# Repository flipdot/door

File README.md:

# door

Door control system for the flipdot hackspace. It runs on a Raspberry Pi at the
door together with a custom PCB in Raspberry Pi HAT form factor
(`pihat_door`).

The current door control system is
**[flipdot/flipdoor](https://code.flipdot.org/flipdot/flipdoor)**, a Rust
project with web and SSH interfaces that serves
[door.flipdot.space](https://door.flipdot.space). The Python implementation in
this repository is legacy and no longer maintained. The sections below
document that implementation and the hardware, which remain useful for
reference.

The system:

- continuously reads the door state (open/closed) from a switch on the door
- unlocks/locks the door on request
  - from a [web frontend](https://door.flipdot.space) (flipdot LDAP login,
    opening is restricted to flipdot members)
  - via RFID: members scan their card with a USB RFID reader
  - via MQTT close commands
- publishes the door state to `api.flipdot.org`, where it is displayed on the
  flipdot.org status page

## Repository layout

| Path | Description |
| --- | --- |
| `hardware/` | KiCad project for the `pihat_door` PCB |
| `door_firmware.X/` | Firmware for the PIC microcontroller on the HAT (MPLAB X project, XC8, PIC16LF1719) |
| `door_lib.py` | Shared Python library: serial access, door state, open/close, API update |
| `web.py` | Flask web frontend (login via LDAP, door state, open/close) |
| `mqtt2door.py` | MQTT bridge + RFID reader daemon |
| `door.py` | Small script that reads the door state and logs it to syslog |
| `door_state.sh` | Shell helper that reads the door state from the serial port |
| `acme.py`, `acme.sh/` | (legacy) TLS via Let's Encrypt/acme.sh; TLS is now handled by nginx |
| `door-master.nginx.conf` | Example nginx configuration (TLS, reverse proxy) |
| `web.service`, `mqtt2door.service` | systemd units |
| `sync.sh` | Syncs `authorized_keys` for the `opendoor` user from LDAP |
| `sync_rfid_tags.sh` | Regenerates `rfid_tags.json` (employee numbers) from LDAP |
| `config.example.py` | Configuration template (copy to `config.py`, see below) |

The `ldap_user/` and `acme.sh/` submodules provide LDAP authentication and
certificate handling respectively.

## Hardware and serial protocol

The HAT carries a PIC16LF1719 that is wired to the Raspberry Pi GPIO header.
It talks over a UART at 9600 baud 8N1 (`config.SERIAL`, default
`/dev/ttyAMA0`).

The PIC continuously samples the door switch (ADC, averaged over 30 samples)
and prints one line per batch:

```
<adc> - <ra0>\r\n
```

- `<adc>`: 10-bit average of the door switch reading; values `> 500` mean the
  door is **open**
- `<ra0>`: digital input on pin RA0

Commands (single character, no newline required):

- `1` – pulse the door open (~200 ms)
- `0` – pulse the door closed (~200 ms)
- anything else – echoed back

The PIC sends `b` at startup and `r` (followed by a UART re-init) when it hits
a UART over-error. `door_lib.get_state()` skips lines that do not start with a
number, so these are handled transparently.

## Web frontend

`web.py` is a small Flask app:

- login with flipdot LDAP credentials (`ldap_user` submodule)
- shows the current door state (10 s cache, or fake data when
  `config.fake_door` is set)
- "open door" button – only usable by flipdot members
  (`is_member` LDAP attribute)
- "close door" button

```sh
pip install -r requirements.txt
cp config.example.py config.py  # adjust DOMAIN, EMAIL, SERIAL, ...
./web.py
```

For production it runs under systemd (`web.service`) behind nginx
(`door-master.nginx.conf`), which terminates TLS.

Set `fake_door = True` in `config.py` to run the app without the hardware.

## MQTT and RFID

`mqtt2door.py` (run under systemd as `mqtt2door.service`) does three things:

1. Connects to the MQTT broker at `power.flipdot.space:1883` and closes the
   door on the `actor/door/close` topic (plus a raw ESP sensor topic).
2. Polls the USB RFID reader on `/dev/ttyUSB0`. If the scanned tag is in
   `rfid_tags.json`, the door is opened, otherwise the event is only logged.
   `sync_rfid_tags.sh` regenerates `rfid_tags.json` from the `employeeNumber`
   attributes of all LDAP members, so member cards work automatically.
3. Publishes the door state to
   `https://api.flipdot.org/sensors/door/locked/<0|1>` every 60 seconds.

## Firmware

`door_firmware.X/` is an MPLAB X project for the PIC16LF1719 on the HAT
(build with the XC8 compiler, e.g. via MPLAB X IDE). See
`hardware/pihat_door.pro` for the board design.

## Configuration

Copy `config.example.py` to `config.py` (git-ignored) and adjust:

| Key | Meaning |
| --- | --- |
| `PORT`, `HTTPS_PORT` | Ports for the Flask app |
| `SERIAL` | Serial device of the HAT, e.g. `/dev/ttyAMA0` |
| `DOMAIN`, `EMAIL` | Domain and contact for certificate issuance |
| `DEBUG` | Verbose logging |
| `STAGING` | Use the Let's Encrypt staging server |
| `fake_door` | Simulate the door state (for development) |

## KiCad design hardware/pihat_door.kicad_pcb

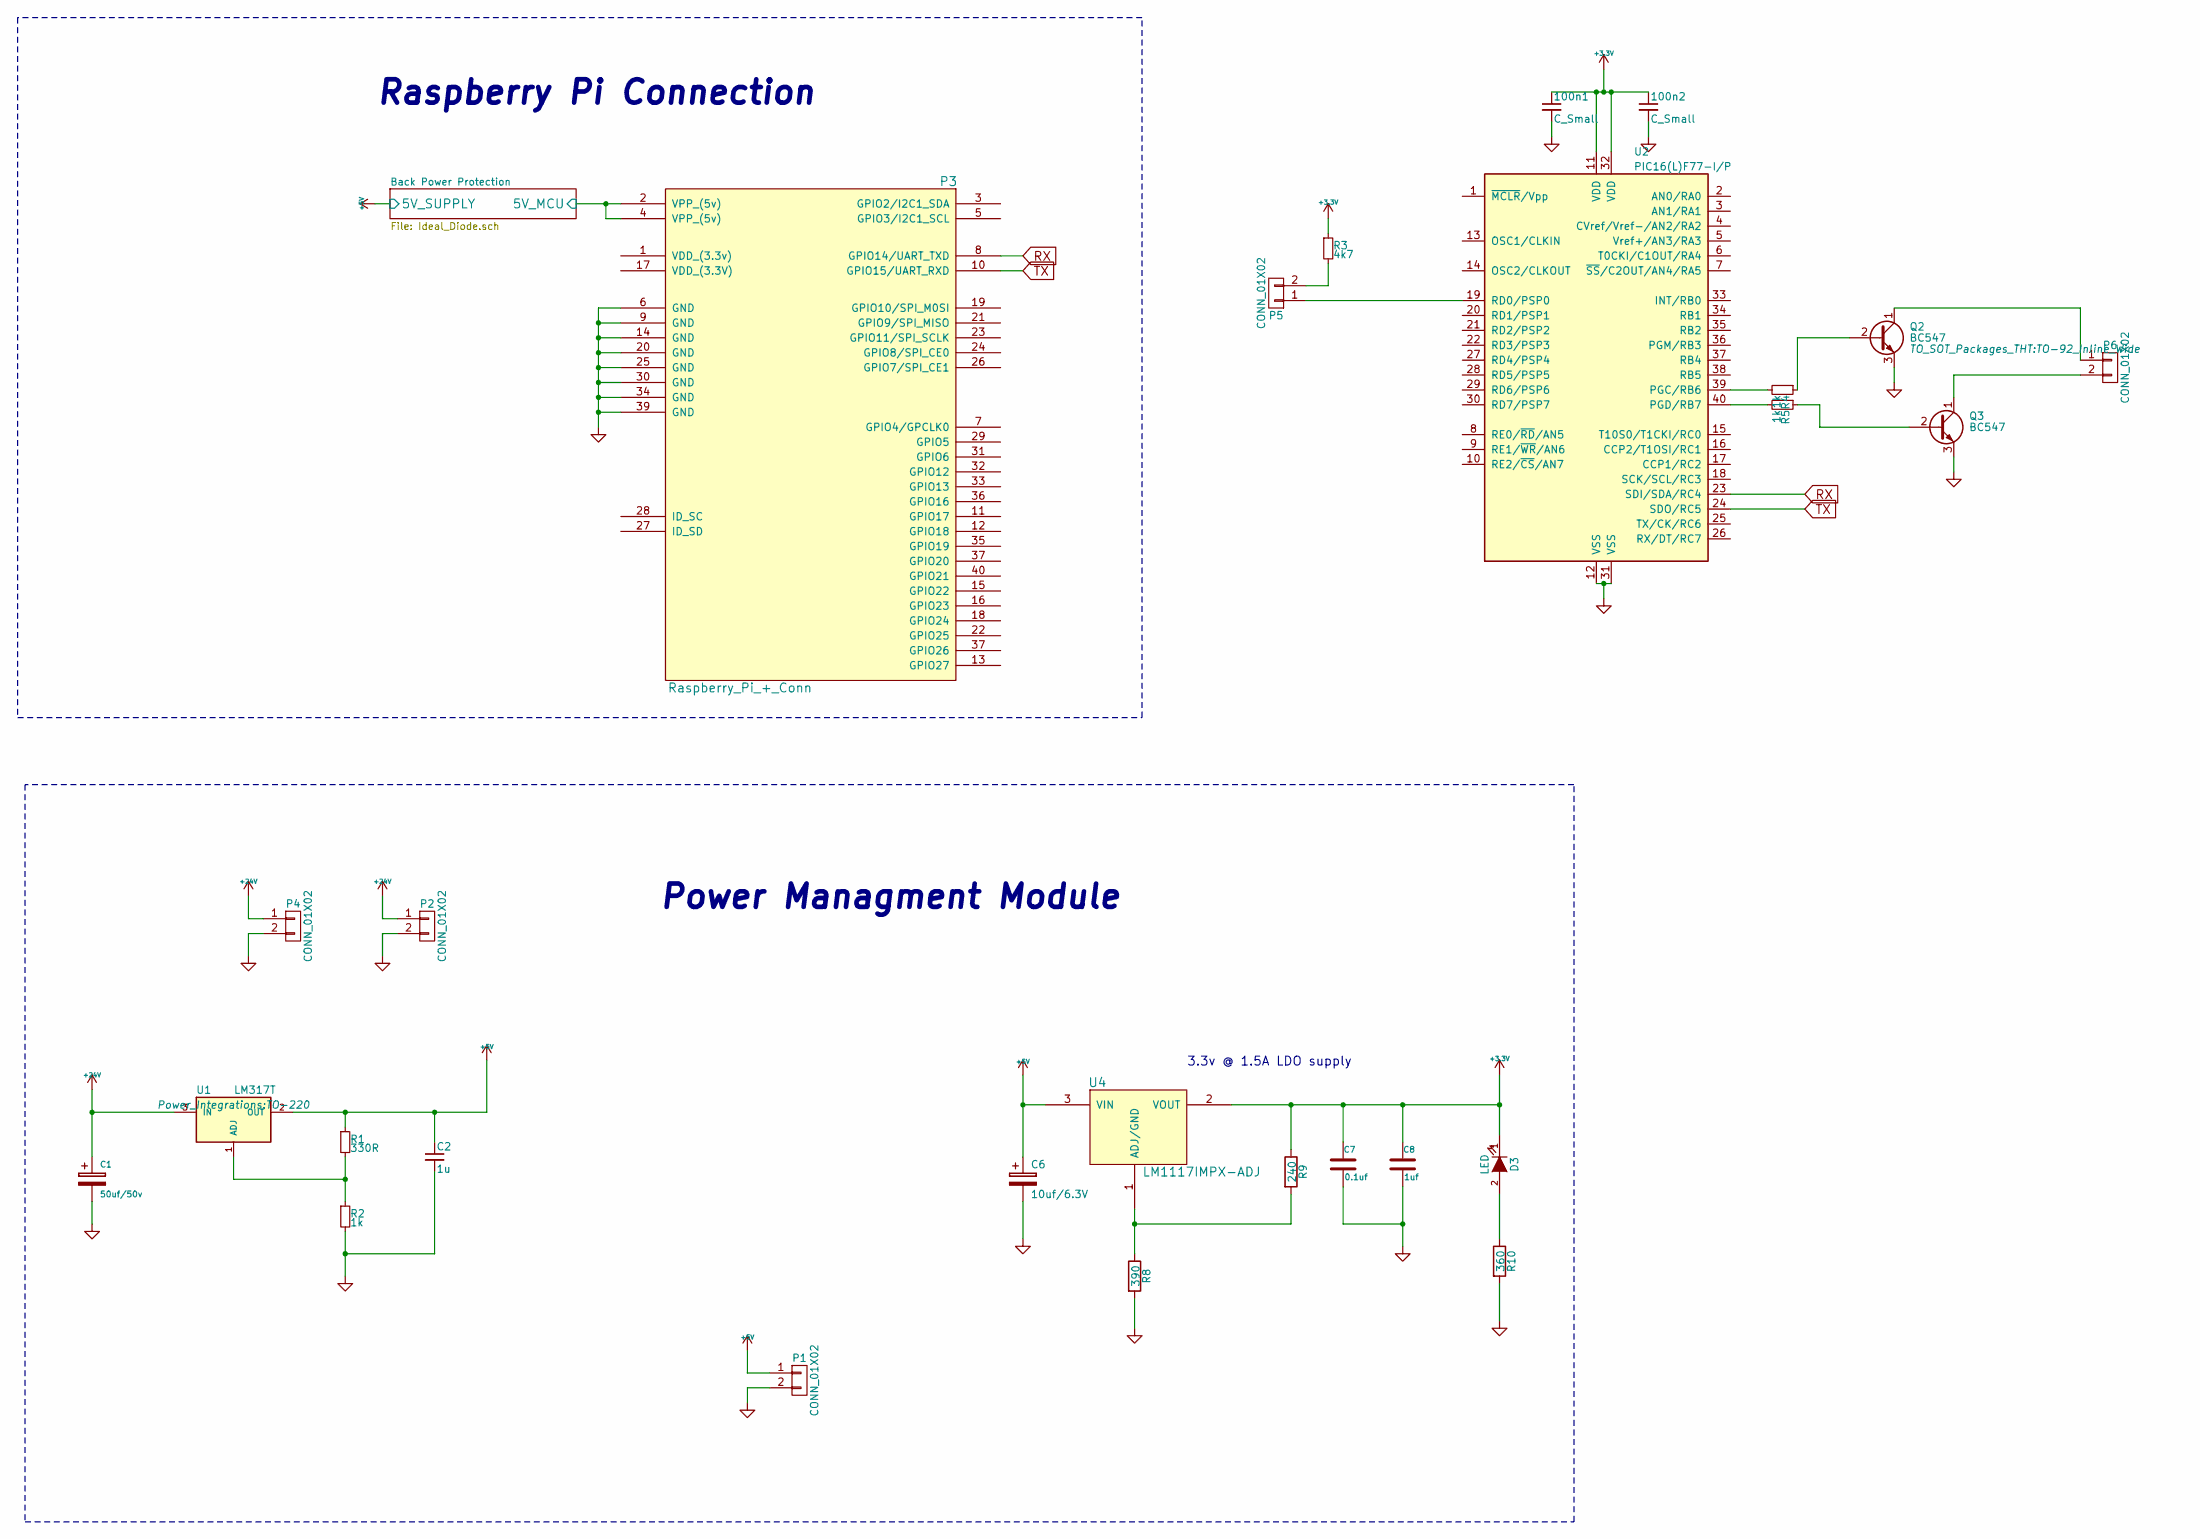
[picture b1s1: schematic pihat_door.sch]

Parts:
100n1, 100n2: C_Small; C_0805_HandSoldering
C1: 50uf/50v; c_elec_6.3x7.7; Mouser Part No. 647-UUR1H470MCL6GS
C2: 1u; c_elec_6.3x7.7
C6: 10uf/6.3V; c_elec_6.3x7.7; Mouser Part No. 5985-AVS16V100-F
C7: 0.1uf; C_0805_HandSoldering; Mouser Part No. 810-C1005X5R1H104K
C8: 1uf; C_0805_HandSoldering; Mouser Part No. 810-C1005X5R1H104K
D3: LED; LED-3MM; Mouser Part No. 743-HT-191USD
P1, P5, P6: CONN_01X02; AK300-2
P2, P4: CONN_01X02; PINHEAD1-2; Mouser Part No. 651-1904383
P3: Raspberry_Pi_+_Conn; IDC_Header_Straight_40pins; Mouser Part No. 517-30340-6002
Q2, Q3: BC547; TO-92_Inline_Wide
R1: 330R; R_0805_HandSoldering
R2, R4, R5: 1k; R_0805_HandSoldering
R3: 4k7; R_0805_HandSoldering
R8: 390; R_0805_HandSoldering; Mouser Part No. 594-MCT06030C3900FP5
R9: 240; R_0805_HandSoldering; Mouser Part No. 754-RR0816P-241D
R10: 360; R_0805_HandSoldering; Mouser Part No. 71-CRCW0603316RFKEB
U1: LM317T; TO-220
U2: PIC16(L)F77-I/P; DIP-40_W15.24mm
U4: LM1117IMPX-ADJ; TO-220; Mouser Part No. 926-M1117IMPXADJNOPB

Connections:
+3V3: 100n1.1, 100n2.1, C7.1, C8.1, D3.1 (K), R3.1, R9.1, U2.11 (VDD), U2.32 (VDD), U4.2 (VOUT)
+5V: C2.1, C6.1, P1.1, R1.1, U1.2 (OUT), U4.3 (VIN); also elsewhere on the board
+24V: C1.1, P2.1, P4.1, U1.3 (IN)
/Back Power Protection/5V_MCU: P3.2 (VPP_(5v)), P3.4 (VPP_(5v)); also elsewhere on the board
GND: 100n1.2, 100n2.2, C1.2, C2.2, C6.2, C7.2, C8.2, P1.2, P2.2, P3.6 (GND), P3.9 (GND), P3.14 (GND), P3.20 (GND), P3.25 (GND), P3.30 (GND), P3.34 (GND), P3.39 (GND), P4.2, Q2.3 (E), Q3.3 (E), R2.2, R8.2, R10.2, U2.12 (VSS), U2.31 (VSS); also elsewhere on the board
unnamed: D3.2 (A), R10.1
unnamed: P5.1, U2.19 (RD0/PSP0)
unnamed: P5.2, R3.2
unnamed: P6.1, Q2.1 (C)
unnamed: P6.2, Q3.1 (C)
unnamed: Q2.2 (B), R4.1
unnamed: Q3.2 (B), R5.1
unnamed: R1.2, R2.1, U1.1 (ADJ)
unnamed: R4.2, U2.39 (PGC/RB6)
unnamed: R5.2, U2.40 (PGD/RB7)
unnamed: R8.1, R9.2, U4.1 (ADJ/GND)
RX: P3.8 (GPIO14/UART_TXD), U2.23 (SDI/SDA/RC4)
TX: P3.10 (GPIO15/UART_RXD), U2.24 (SDO/RC5)

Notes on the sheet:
Raspberry Pi Connection
Power Managment Module
3.3v @ 1.5A LDO supply

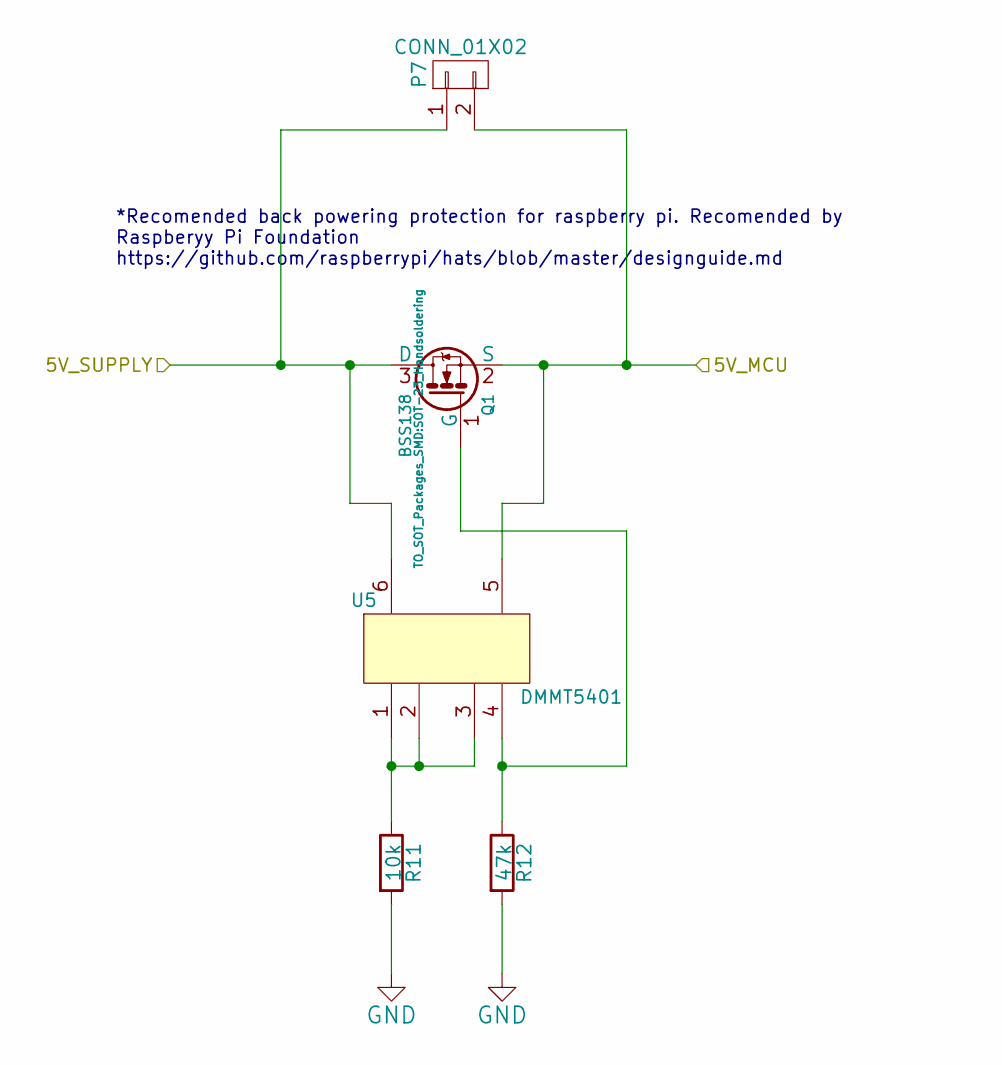
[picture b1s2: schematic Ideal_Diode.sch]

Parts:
P7: CONN_01X02; PINHEAD1-2
Q1: BSS138; SOT-23_Handsoldering; Mouser Part No. 621-DMG2305UX-13
R11: 10k; R_0805_HandSoldering; Mouser Part No. 71-CRCW0402-10K-E3
R12: 47k; R_0805_HandSoldering; Mouser Part No. 667-ERJ-2RKF4702X
U5: DMMT5401; SOT-23-6; Mouser Part No. 621-DMMT5401-7-F

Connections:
+5V: P7.1, Q1.3 (D), U5.6; also elsewhere on the board
/Back Power Protection/5V_MCU: P7.2, Q1.2 (S), U5.5; also elsewhere on the board
GND: R11.2, R12.2; also elsewhere on the board
unnamed: Q1.1 (G), R12.1, U5.4
unnamed: R11.1, U5.1, U5.2, U5.3

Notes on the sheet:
*Recomended back powering protection for raspberry pi. Recomended by Raspberyy Pi Foundation https://github.com/raspberrypi/hats/blob/master/designguide.md

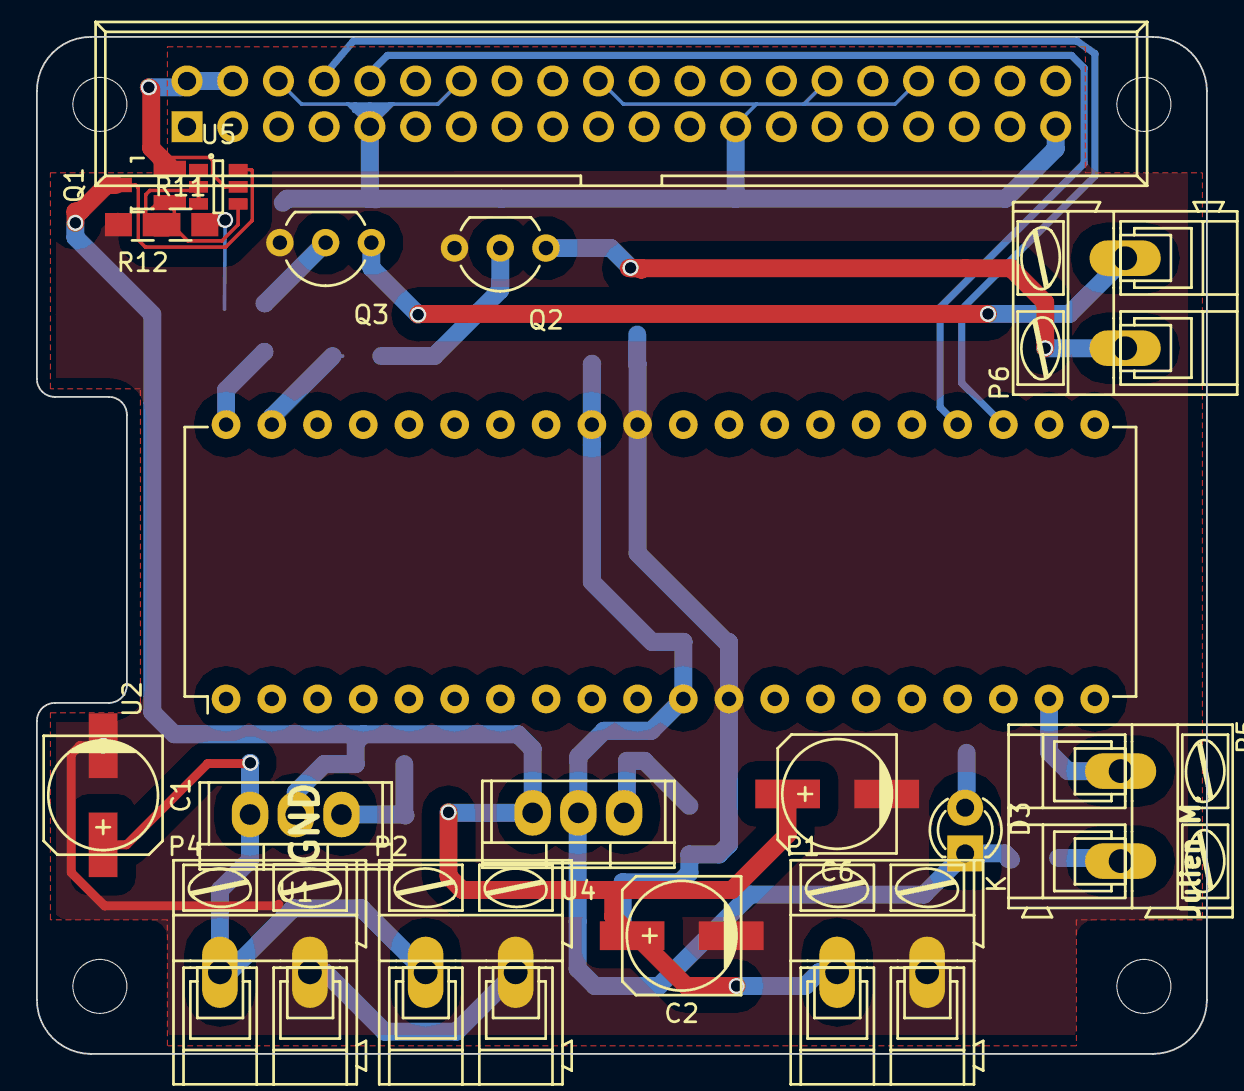
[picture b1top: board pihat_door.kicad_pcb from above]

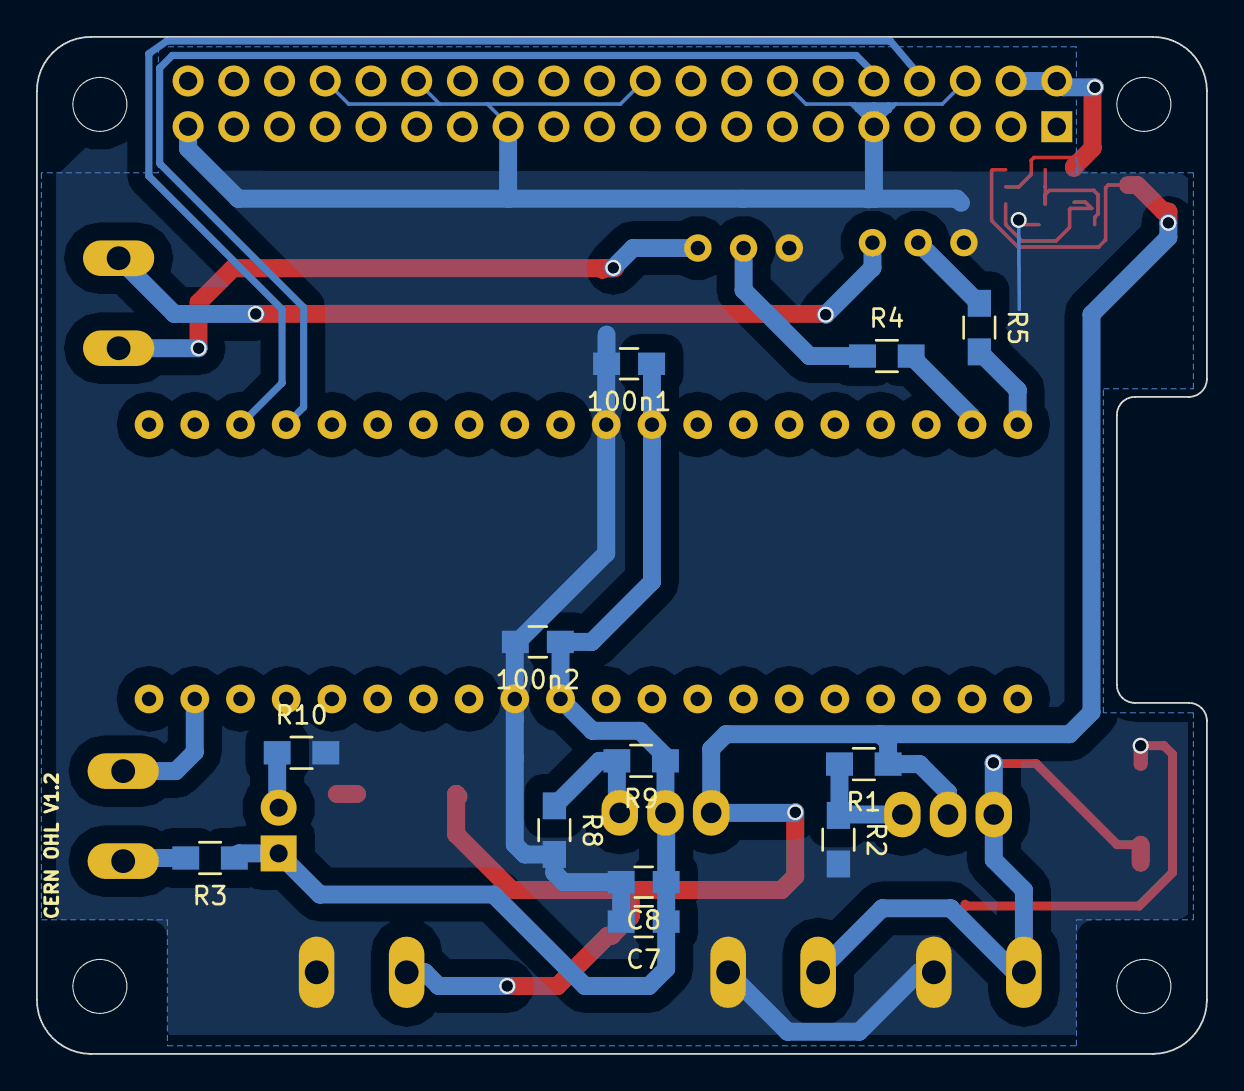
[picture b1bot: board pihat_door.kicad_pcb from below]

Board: 2 copper layers, 65.0 x 56.5 mm, 31 parts (12 on the bottom side), 20 nets.

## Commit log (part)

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2018-01-24 add hardware schematic and layout files
2018-01-24 add pic source
2018-01-24 fix of by on error
2018-01-25 add mqtt endpoint. replace shell by python script
2018-02-13 Added intellij fodder
2018-02-13 Added door_lib which abstracts away door handling @malled2002 please review
2018-02-13 Added basic WebApp for opening/closing door with LDAP logins please review :D
2018-02-16 add requirements
2018-02-17 add missing argument
2018-02-19 [WIP]: door.fd: add acme.sh wrapper
2018-02-21 Fix door webinterface with everything!
2018-02-21 added door master
2018-03-27 show some more information in door state
2018-03-27 fake_door for example config
2018-03-27 send door lock state to api when locking/unlocking
2018-03-27 fix send_api
2018-05-04 door_lib: add status updater (every 10 secs) to mqtt2door service
2019-06-02 logging and rfid
2019-06-02 add stateless param
2019-06-02 more logs
2019-06-02 disable acme
2019-06-02 use more https
2019-06-02 add rfid sync script
2019-06-02 ugly i2c port
2019-06-09 add door close btn
2019-06-09 remove old schematics and firmware files
2019-06-09 remove serial reader and mqtt endpoint
2019-06-09 add esp32 code
2019-06-09 more readable i2c cmds
2019-06-09 add door open function
2019-12-10 commit current state...
2019-12-10 add logging
2019-12-10 merge?
2019-12-10 add report
2021-08-03 fix everything
2023-02-01 switch to python3
2023-02-01 add summer
2023-02-15 Install black
2023-02-15 Add manifest template
2023-02-15 Remove optional closing tag
2023-02-15 Copy base templates from submodule
2023-02-15 Return manifest.json
2023-02-15 Also return a proper content type
2023-02-15 Fix import errors
2023-02-15 Reference manifest

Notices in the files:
hardware/pihat_door.kicad_pcb:
License: CERN OHL V1.2
CERN OHL V1.2
